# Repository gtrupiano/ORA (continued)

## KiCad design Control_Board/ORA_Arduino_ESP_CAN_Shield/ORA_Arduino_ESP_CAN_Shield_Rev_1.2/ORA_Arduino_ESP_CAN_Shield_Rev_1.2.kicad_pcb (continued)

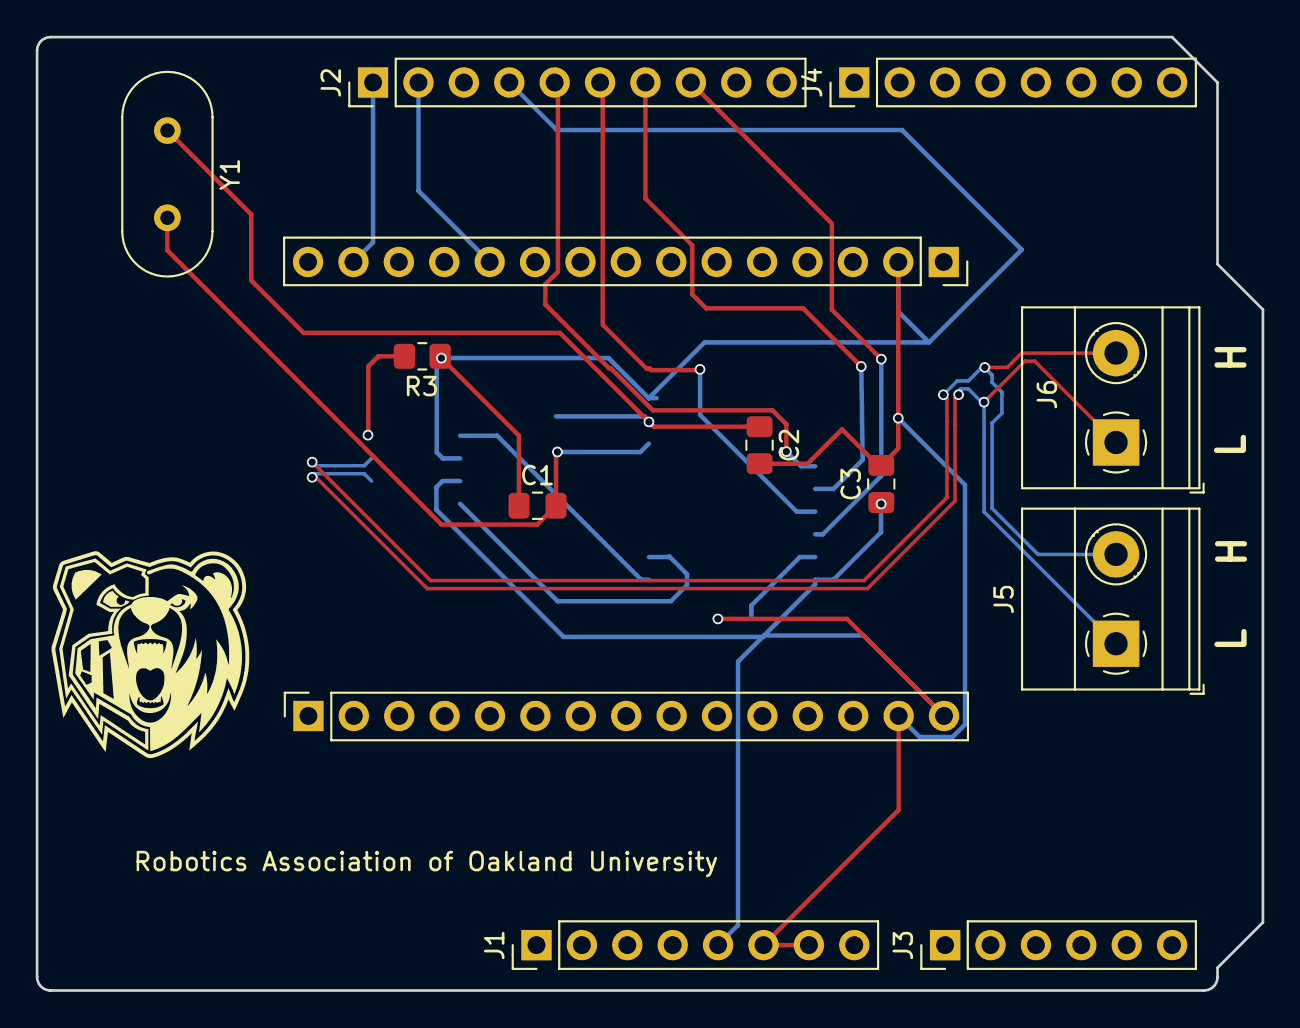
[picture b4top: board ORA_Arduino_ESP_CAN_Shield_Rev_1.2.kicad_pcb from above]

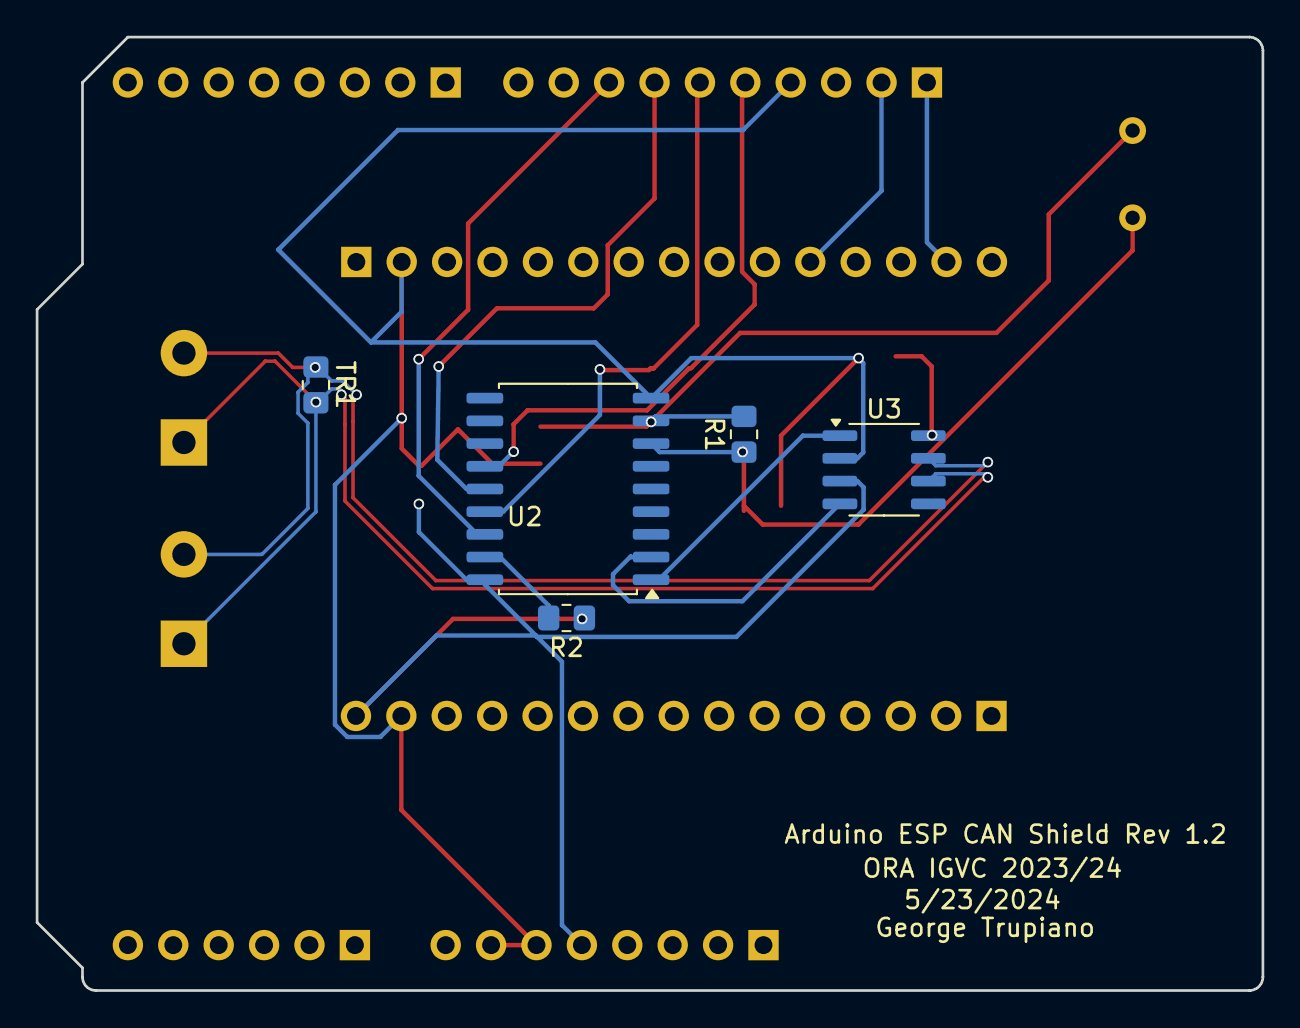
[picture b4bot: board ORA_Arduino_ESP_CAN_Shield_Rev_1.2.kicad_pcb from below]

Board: 2 copper layers, 68.6 x 53.3 mm, 17 parts (5 on the bottom side), 16 nets.

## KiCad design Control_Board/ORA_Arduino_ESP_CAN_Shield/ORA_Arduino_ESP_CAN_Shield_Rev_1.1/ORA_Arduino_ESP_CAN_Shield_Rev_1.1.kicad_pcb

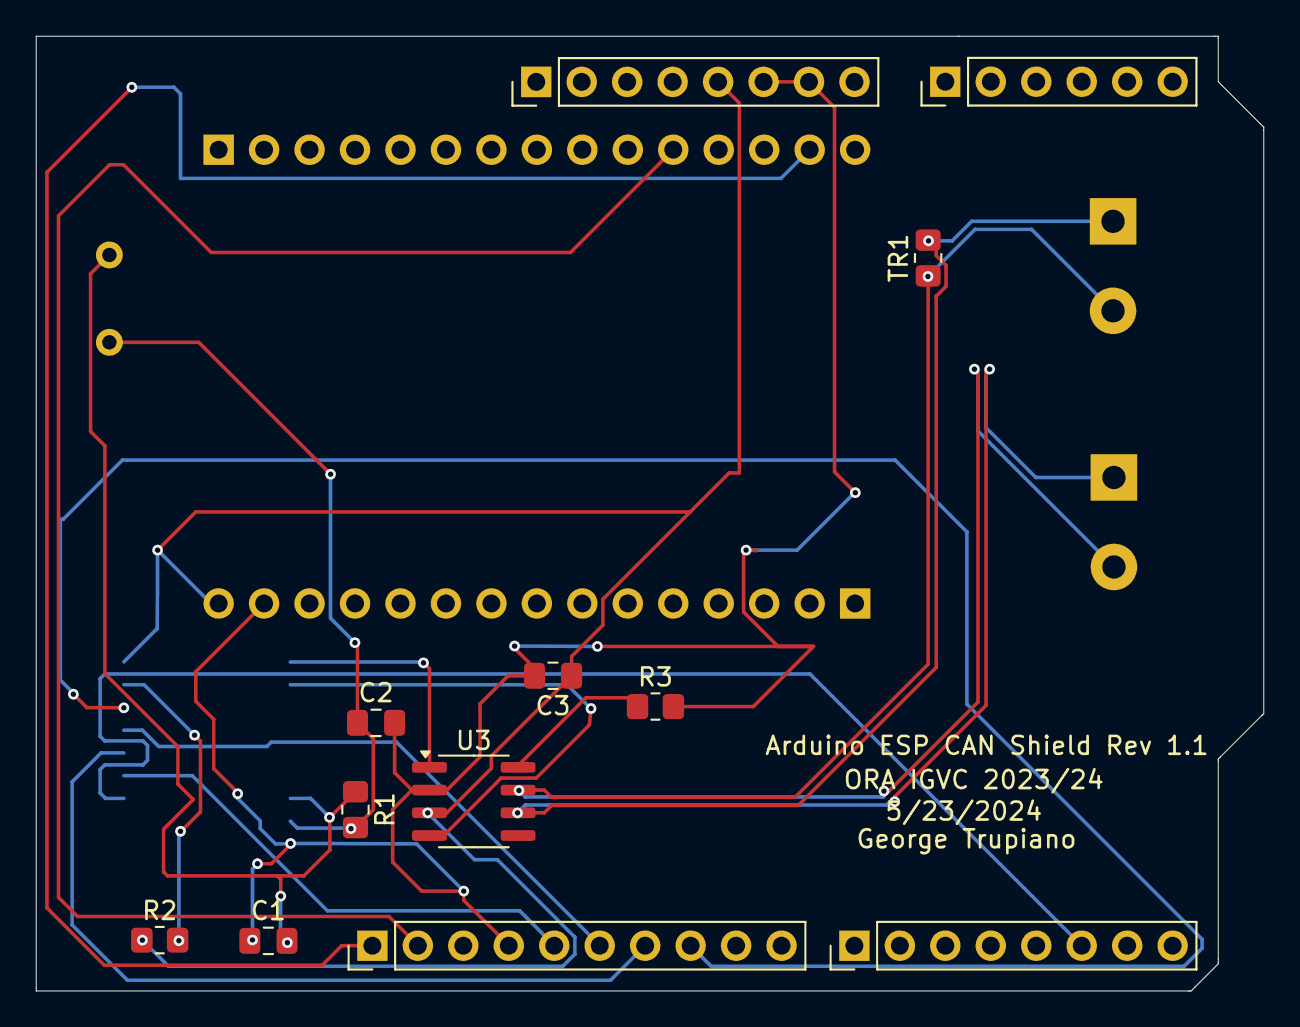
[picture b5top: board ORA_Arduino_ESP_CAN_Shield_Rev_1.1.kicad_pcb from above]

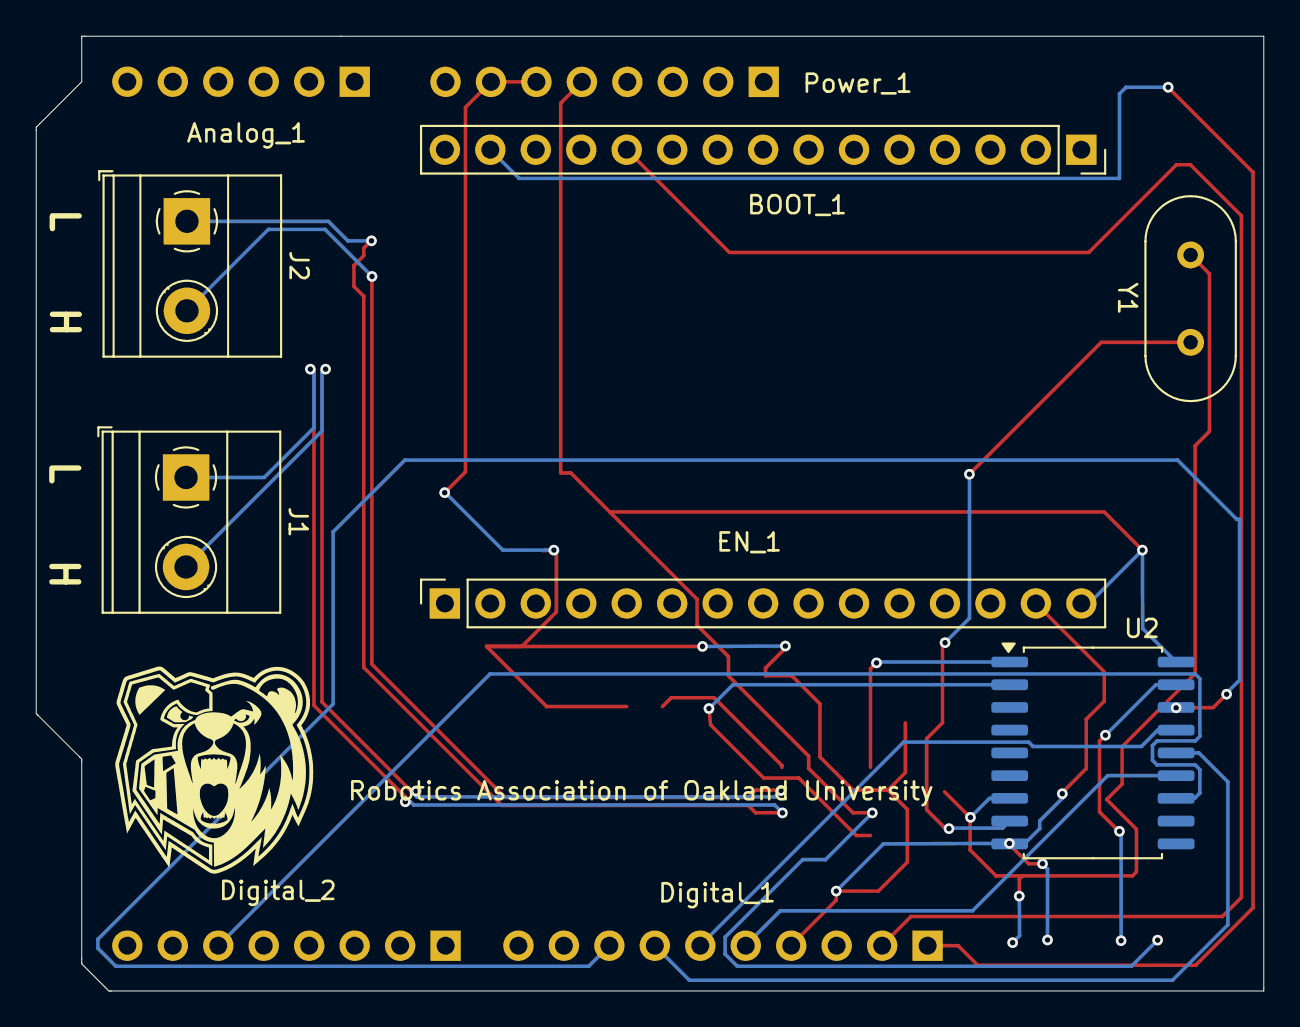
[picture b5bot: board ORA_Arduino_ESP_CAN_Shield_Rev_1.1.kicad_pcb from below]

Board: 2 copper layers, 68.6 x 53.3 mm, 18 parts (6 on the bottom side), 17 nets.

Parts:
Analog_1: Conn_01x06; PinHeader_1x06_P2.54mm_Vertical
BOOT_1: Conn_01x15; PinSocket_1x15_P2.54mm_Vertical
C1, C2: 22pF; C_0805_2012Metric_Pad1.18x1.45mm_HandSolder
C3: 100nF; C_0805_2012Metric_Pad1.18x1.45mm_HandSolder
Digital_1: Conn_01x10; PinHeader_1x10_P2.54mm_Vertical
Digital_2: Conn_01x08; PinHeader_1x08_P2.54mm_Vertical
EN_1: Conn_01x15; PinSocket_1x15_P2.54mm_Vertical
J1, J2: CAN; TerminalBlock_Phoenix_MKDS-1,5-2_1x02_P5.00mm_Horizontal
Power_1: Conn_01x08; PinHeader_1x08_P2.54mm_Vertical
R1: 1M; R_0805_2012Metric_Pad1.20x1.40mm_HandSolder
R2, R3: 10k; R_0805_2012Metric_Pad1.20x1.40mm_HandSolder
TR1: 120; R_0805_2012Metric_Pad1.20x1.40mm_HandSolder
U2: MCP2515-xSO; SOIC-18W_7.5x11.6mm_P1.27mm
U3: MCP2551-I-SN; SOIC-8_3.9x4.9mm_P1.27mm
Y1: 8Mhz; Crystal_HC49-4H_Vertical

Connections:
+5V: C3.1, EN_1.15, Power_1.5, R2.1, U2.18 (VDD), U3.3 (VDD)
CAN+: J1.2, J2.2, TR1.1, U3.7 (CANH)
CAN-: J1.1, J2.1, TR1.2, U3.6 (CANL)
CS: Digital_1.8, U2.16 (~CS)
GND: C1.1, C2.2, C3.2, Digital_1.4, EN_1.14, Power_1.6, Power_1.7, R3.2, U2.9 (VSS), U3.2 (VSS)
INT: Digital_2.6, U2.12 (~INT)
unnamed: C2.1, R1.2, U2.8 (OSC1), Y1.1
unnamed: C1.2, R1.1, U2.7 (OSC2), Y1.2
unnamed: U2.2 (RXCAN), U3.4 (RXD)
unnamed: U2.1 (TXCAN), U3.1 (TXD)
unnamed: R2.2, U2.17 (~RESET)
unnamed: R3.1, U3.8 (Rs)
SCK: Digital_1.5, U2.13 (SCK)
SCL: BOOT_1.14, Digital_1.1
SDA: BOOT_1.11, Digital_1.2
SI: Digital_1.7, U2.14 (SI)
SO: Digital_1.6, U2.15 (SO)

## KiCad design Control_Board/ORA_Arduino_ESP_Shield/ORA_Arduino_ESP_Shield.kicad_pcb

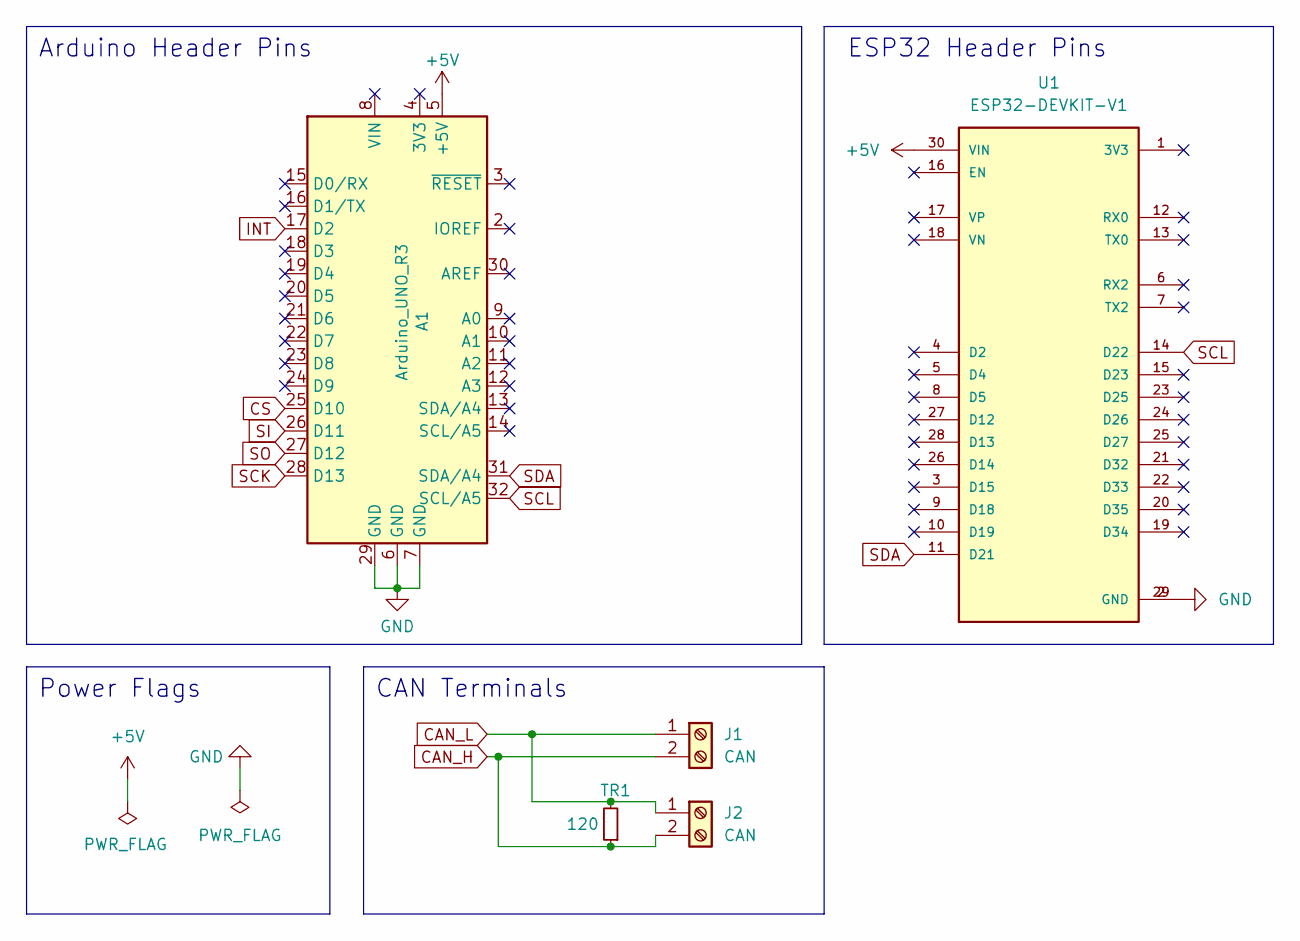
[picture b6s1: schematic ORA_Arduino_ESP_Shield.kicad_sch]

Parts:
A1: Arduino_UNO_R3
J1, J2: CAN; TerminalBlock_Phoenix_MKDS-1,5-2_1x02_P5.00mm_Horizontal
TR1: 120; R_0805_2012Metric_Pad1.20x1.40mm_HandSolder
U1: ESP32-DEVKIT-V1; ESP32_DEVKIT_V1_MODULE; PARTREV N/A

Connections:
+5V: A1.5 (+5V), U1.30 (VIN)
CAN_H: J1.2, J2.2, TR1.1
CAN_L: J1.1, J2.1, TR1.2
CS: A1.25 (D10)
GND: A1.6 (GND), A1.7 (GND), A1.29 (GND), U1.2 (GND), U1.29 (GND)
INT: A1.17 (D2)
SCK: A1.28 (D13)
SCL: A1.32 (SCL/A5), U1.14 (D22)
SDA: A1.31 (SDA/A4), U1.11 (D21)
SI: A1.26 (D11)
SO: A1.27 (D12)

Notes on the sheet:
Power Flags
Arduino Header Pins
CAN Terminals
ESP32 Header Pins

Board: 2 copper layers, 5 parts (1 on the bottom side), 6 nets, no tracks yet.

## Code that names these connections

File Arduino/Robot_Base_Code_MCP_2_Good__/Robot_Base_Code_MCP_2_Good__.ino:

#include <PS4Controller.h>
#include <mcp_can.h>
#include <SPI.h>

// digital pins available on control board: 0, 1, 10, 5, 13
// analog pins available on control board: 0, 1, 2, 3, 4

// CAN / ODrive Declarations
#define ODRV0_NODE_ID 0 // Left Motor
#define ODRV1_NODE_ID 1 // Right Motor
#define CAN0_INT 2    // Set INT to pin 2 (This is the Interrupt pin)
#define CAN_BAUDRATE 500000
MCP_CAN CAN0(17);   // Set CS to pin 17 (This is the Chip select)

#define EStop 0         // Hardware EStop

// IMU Declarations
#define IMU_SCL 3 // On AtMega32U4 Connected to Pin 18 (PD0)
#define IMU_SDA 2 // On AtMega32U4 Connected to Pin 19 (PD1)

// LED Declarations
#define LEDPWR_R 4 // On AtMega32U4 Connected to Pin 25 (PD4)
#define LEDPWR_G 12 // On AtMega32U4 Connected to Pin 26 (PD6)
#define LEDPWR_B 6 // On AtMega32U4 Connected to Pin 27 (PD7)

// Battery Voltage Detection Declaration
#define Battery_Voltage A0 // On AtMega32U4 Connected to Pin 27 (PF0)

double verticalMov = 0;
double horizontalMov = 0;
bool EStopButton = false;
bool EStopState = false;

void setup()
{
  pinMode(CAN0_INT, INPUT);

  pinMode(IMU_SCL, INPUT);
  pinMode(IMU_SDA, INPUT);

  pinMode(LEDPWR_R, INPUT);
  pinMode(LEDPWR_G, INPUT);
  pinMode(LEDPWR_B, INPUT);

  Serial.begin(115200);

  // MAC Address for my controller
  PS4.begin("bc:03:58:28:67:42");
  Serial.println("Ready");

  // Continuously tries to establish connection to MCP chip until it does
  while(1)
  {
    // Tries to initialize MCP CAN chip with clock of 8MHz and data transfer speed is 500KB/second
    if(CAN0.begin(MCP_ANY, CAN_500KBPS, MCP_8MHZ) == CAN_OK)
    {
      Serial.println("MCP2515 Initialized Successfully!");
      break;
    }
    else 
    {
      Serial.println("Error Initializing MCP2515...");
      delay(20);
    }
  }
}

void loop() 
{
  // For obtaining values, have arduino and esp work seperatly. Use I2C for communicating between the two
  if(PS4.isConnected()) // could combine with If statement below but this is easier to read for now
  {
    verticalMov = PS4.LStickY(); // Possibly add some error detection (debounce)?
    horizontalMov = PS4.LStickX();
    EStopButton = PS4.R1();

    Serial.print("X: ");
    Serial.print(verticalMov);
    Serial.print("  Y: ");
    Serial.println(horizontalMov);
  }
  else
  {
    verticalMov = 0;
    horizontalMov = 0;
  }

  // Allows EStop to be toggled
  if(EStopButton && !EStopState)
  {
    // Send EStop command to ODrive
    ODriveEStop();
    EStopState = true;
  }
  else if(EStopButton && EStopState)
  {
    ODriveControlState();
    ODriveMovement(verticalMov, horizontalMov);
    EStopState = false;
  }
}

// Converts Joystick values into Revolutions/Second and sends data to ODrive over CAN
void ODriveMovement(double verticalVelocity, double horizontalVelocity) // redo math for turns/second
{
  // Scales inputs
  verticalVelocity = constrain(verticalVelocity, -1.0, 1.0);
  horizontalVelocity = constrain(horizontalVelocity, -1.0, 1.0);

  // Standard for differential drive control
  double leftMotorVel = verticalVelocity - horizontalVelocity;
  double rightMotorVel = verticalVelocity + horizontalVelocity;

  // Converts the velocity requested into Revolutions / second
  const int maxVelocity = 5; // IGVC rules, should be meters/second units but not sure
  const double wheelCircumference = 2 * M_PI * 0.1524; // Circumference of the wheel in meters
  double leftMotorRPS= (leftMotorVel * maxVelocity) / wheelCircumference; // Turns/second
  double rightMotorRPS = (rightMotorVel * maxVelocity) / wheelCircumference; // Turns/second

  // Send velocity CAN commands to left and right motors
  CAN0.sendMsgBuf((ODRV0_NODE_ID << 5 | 0x0D), 0, 4, (byte*)&leftMotorRPS); // check 4
  CAN0.sendMsgBuf((ODRV1_NODE_ID << 5 | 0x0D), 0, 4, (byte*)&rightMotorRPS);
}

// Send CAN command to ODrive to initate EStop
void ODriveEStop()
{
  CAN0.sendMsgBuf((ODRV0_NODE_ID << 5 | 0x02), 0, 0, nullptr);
  CAN0.sendMsgBuf((ODRV1_NODE_ID << 5 | 0x02), 0, 0, nullptr);
  Serial.println("EStop Activated");
}

// Send CAN command to put axis into closed loop control state
void ODriveControlState() // Could combine with estop function but meh
{
  CAN0.sendMsgBuf((ODRV0_NODE_ID << 5 | 0x07), 0, 4, (byte*)"\x08");
  CAN0.sendMsgBuf((ODRV1_NODE_ID << 5 | 0x07), 0, 4, (byte*)"\x08");
  Serial.println("Put into closed loop control state");
}

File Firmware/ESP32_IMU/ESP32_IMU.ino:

/*
 **********************************************************************
 * INCLUDES
 **********************************************************************
*/

#include "ESP32_IMU.hpp"

/*
 **********************************************************************
 * DEFINES and CONSTANTS
 **********************************************************************
*/

/*
 **********************************************************************
 * GLOBAL VARIABLES
 **********************************************************************
*/

TaskTime_t tasks = 
{
    // {period, lastTime}
    .printImu = {60, 0},
    .led = {500, 0}
};

IMU_t imu = {};
BNO08x bno;

/*
 **********************************************************************
 * LOCAL TYPES
 **********************************************************************
*/

/*
 **********************************************************************
 * LOCAL VARIABLES (declare as static)
 **********************************************************************
*/

/*
 **********************************************************************
 * LOCAL FUNCTION PROTOTYPES (declare as static)
 **********************************************************************
*/
  
/*
 **********************************************************************
 * GLOBAL FUNCTIONS
 **********************************************************************
*/


void setup() 
{
    Serial.begin(115200);

    pinMode(LED_PIN, OUTPUT);

    // Setting up IMU
    bool imuConfigSuccessful = configureIMU();

    if(imuConfigSuccessful == false)
    {
        while(1)
        {
            Serial.println("An issue occured during configuration. Please look at serial logs to determine error and then try again.");
            delay(5000);
        }
    }
    else
    {
        Serial.println("IMU ready!");
    }
    
    delay(100);

    // Configuring all tasks last updated time
    unsigned long currTime = millis();
    tasks.printImu.lastTime = currTime;
    tasks.led.lastTime = currTime;

}


void loop() 
{
    /*
        Since IMU update needs to be called frequently so fusion filter 
        can be computed, other slower tasks need to be kept track of
        in terms of their timing. So checking the time of them is needed.
    */
    unsigned long currentTime = millis();

    if (bno.wasReset()) 
    {
        Serial.print("Sensor was reset ");
        imuOutputDataConfig();
    }

    // Fetching data from IMU and updating IMU struct
    updateImuObject();

    // Only print data when time proper amount of time has elapsed
    if((currentTime - tasks.printImu.lastTime) >= tasks.printImu.period)
    {
        bool printAccel = true; 
        bool printGyro = true;
        bool printQuat = true;

        printImuData(printAccel, printGyro, printQuat);
        
        // Updating time here since it is possible that when it's time to print data, that the IMU wasn't ready to update.
        tasks.printImu.lastTime = currentTime;
    }

    if((currentTime - tasks.led.lastTime) >= tasks.led.period)
    {
        digitalWrite(LED_PIN, !digitalRead(LED_PIN));
        tasks.led.lastTime = currentTime;
    }

    // Quaternions are computed by the fusion filter and only update when mpu.update() runs frequently. 
    // Keep loop fast; avoid long delays or quat may freeze at (1,0,0,0). 
    delay(1);
}


/*
 **********************************************************************
 * LOCAL FUNCTIONS
 **********************************************************************
*/

/**************************************************
 * Function Name: configureIMU
 * Description: 
**************************************************/

bool configureIMU()
{
    // Configuring communication over I2C
    Wire.begin(IMU_SDA_PIN, IMU_SCL_PIN);
    Wire.setClock(400000);   // 400 kHz I2C fast mode
    Wire.setTimeOut(50);     // prevent long I2C blocking/hanging
    
    delay(250);
    // TODO: Add in a multi attempt to connect to the bno
    
    uint8_t imuConnectAttempts = 0;
    bool imuConnected = false;

    while(imuConnectAttempts < IMU_CONNECT_RETRY_NUM)
    {
        // Setting up IMU with proper interrupt and reset pins
        if(bno.begin(IMU_I2C_ADDRESS, Wire, IMU_INT_PIN, IMU_RST_PIN) == false) 
        {
            Serial.println("IMU connection failed. Please check connection with examples.");
        }
        else
        {
            Serial.println("IMU connection successful");
            imuConnected = true;
            break;
        }

        imuConnectAttempts++;
    }

    // Configuring what data to report
    imuOutputDataConfig();

    return imuConnected;
}


/**************************************************
 * Function Name: imuOutputDataConfig
 * Description: 
**************************************************/

void imuOutputDataConfig()
{
    // Accelerometer data
    if(bno.enableAccelerometer() == true)
    {
        Serial.println("Accelerometer enabled");
    }
    else
    {
        Serial.println("Can't enable  accelerometer");
    }

    // Gyroscopic data
    if(bno.enableGyro() == true)
    {
        Serial.println("Gyro enabled");
    }
    else
    {
        Serial.println("Can't enable  gyro");
    }

    // Rotational vector data (used for quaternions)
    if(bno.enableRotationVector() == true)
    {
        Serial.println(("Rotation vector enabled"));
    }
    else
    {
        Serial.println("Can't enable  rotation vector");
    }
}

/**************************************************
 * Function Name: updateImuObject
 * Description: 
**************************************************/

void updateImuObject()
{
    // Checking whether an event occured
    if(bno.getSensorEvent() == true)
    {
        uint8_t sensorEvent = bno.getSensorEventID();

        switch(sensorEvent)
        {
            case SENSOR_REPORTID_ACCELEROMETER:
                imu.accel.x = bno.getAccelX();
                imu.accel.y = bno.getAccelY();
                imu.accel.z = bno.getAccelZ();
            break;

            case SENSOR_REPORTID_GYROSCOPE_CALIBRATED:
                imu.gyro.x = bno.getGyroX();
                imu.gyro.y = bno.getGyroY();
                imu.gyro.z = bno.getGyroZ();
            break;

            case SENSOR_REPORTID_ROTATION_VECTOR:
                imu.quat.w = bno.getQuatReal();
                imu.quat.x = bno.getQuatI();
                imu.quat.y = bno.getQuatJ();
                imu.quat.z = bno.getQuatK();
                // there is a getQuatRadianAccuracy() but not sure if needed?
            break;

            default:
            break;
        }

        imu.sampleTimeMS = millis();
    }
}


/**************************************************
 * Function Name: printImuData
 * Description: 
**************************************************/

void printImuData(bool accel, bool gyro, bool quat)
    {
    // Printing acceleration data
    if(accel)
    {
        Serial.print("[");
        Serial.print(imu.sampleTimeMS);
        Serial.print("] Acceleration (x,y,z): ");
        Serial.print("X: ");
        Serial.print(imu.accel.x);
        Serial.print(", Y: ");
        Serial.print(imu.accel.y);
        Serial.print(", Z: ");
        Serial.print(imu.accel.z);
        Serial.println(" m/s^2");
        Serial.println();
    }

    // Printing gyroscopic data
    if(gyro)
    {
        Serial.print("[");
        Serial.print(imu.sampleTimeMS);
        Serial.print("] Gyroscope (x,y,z): ");
        Serial.print("X: ");
        Serial.print(imu.gyro.x);
        Serial.print(", Y: ");
        Serial.print(imu.gyro.y);
        Serial.print(", Z: ");
        Serial.print(imu.gyro.z);
        Serial.println(" rad/s");
        Serial.println();
    }

    // Printing quaternion data
    if(quat)
    {
        Serial.print("[");
        Serial.print(imu.sampleTimeMS);
        Serial.print("] Quaternion (w,x,y,z): ");
        Serial.print(imu.quat.w, 6); Serial.print(", ");
        Serial.print(imu.quat.x, 6); Serial.print(", ");
        Serial.print(imu.quat.y, 6); Serial.print(", ");
        Serial.println(imu.quat.z, 6);
        Serial.println();
    }
    
    // Ending line if any value are requested
    if(accel || gyro || quat)
    {
        Serial.println("--------------------------");
        Serial.println();
    }
}

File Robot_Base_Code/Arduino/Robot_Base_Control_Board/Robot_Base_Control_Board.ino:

// States
bool EStopped = false;
bool AutonMode = false;

// Inputs
const int EStopPin = 0;
const int AutonPin = 1;

// Outputs
const int LED_R = 4;
const int LED_G = 12;
const int LED_B = 6;

// Blinking Declarations
unsigned long prevRunTime = 0;
const int blinkInterval = 200;
bool autonLEDState = false;
void AutonRedBlink();
void setup() 
{
  pinMode(EStopPin, INPUT);  // Configure EStop as input signal
  pinMode(AutonPin, INPUT);  // Configure Auton as input signal

  pinMode(LED_R, OUTPUT);
  pinMode(LED_G, OUTPUT);
  pinMode(LED_B, OUTPUT);

  // Initialize LED states
  digitalWrite(LED_R, LOW);
  digitalWrite(LED_G, LOW);
  digitalWrite(LED_B, LOW);
}

void loop() 
{
  EStopped = digitalRead(EStopPin);  // Read the EStop signal
  AutonMode = digitalRead(AutonPin);  // Read the Auton signal

  if (EStopped) 
  { 
    digitalWrite(LED_R, HIGH);
    digitalWrite(LED_G, LOW);
    digitalWrite(LED_B, LOW);
  }
  else 
  { 
    if (AutonMode) 
    {
      AutonRedBlink();
    }
    else 
    {
      digitalWrite(LED_R, LOW);
      digitalWrite(LED_G, HIGH);
      digitalWrite(LED_B, LOW);
    }
  }
  delay(10);
}

void AutonRedBlink()
{
  digitalWrite(LED_B, LOW);
  digitalWrite(LED_G, LOW);

  unsigned long currRunTime = millis();

  if(currRunTime - prevRunTime >= blinkInterval)
  {
    autonLEDState = !autonLEDState;

    digitalWrite(LED_R, autonLEDState ? HIGH : LOW);

    prevRunTime = currRunTime;  // Update the previous run time after toggling
  }
}

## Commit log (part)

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2024-03-12 Base Code updates
2024-03-13 Second Revision
2024-03-13 Getting there?
2024-03-14 Notes
2024-03-18 test
2024-03-19 Update Robot_Base_Code_MCP_2_Good__.ino
    Toggle function for E-Stop implemented
    Movement function adjusted for revolutions per second calculations.
    Declarations done for IMU, LED, etc.
2024-03-21 Library Update
2024-03-21 Made separate program for Control board and ESP32
2024-03-22 Continued
2024-03-23 Basic I2C programs created
    This was just to test whether inputs from controller could be received from ESP and transmitted through I2C to a separate Arduino.
2024-03-24 Deleted Library folder
    Not needed
2024-03-28 Working I2C program
    Controller values are able to be received from ESP and sent to arduino uno.
2024-03-29 Finished testing I2C programs
2024-03-29 Added proper I2C communication
2024-03-29 Comments
2024-04-03 Added control board and reformatting
2024-04-06 Created Robot Base Code using ODriveArduino Library
    Original MCP program was modified to incorperate ODriveArduino Library
2024-04-07 User input made and lib example updated
2024-04-07 Modified receive program
    ESP is being weird but arduino 2 arduino works for I2C
2024-04-08 Fixed data conversion issues
2024-04-08 fixed
2024-04-19 Commented program
2024-04-21 Made rev 2.1
    Still need rev 2
2024-04-21 Rev 2
2024-04-30 Renaming and reorganizing files
2024-04-30 Reorganize
2024-04-30 Renamed
2024-04-30 Renaming
2024-05-03 Added picture
2024-05-03 Pictures Added
2024-05-03 ZED Testing
2024-05-03 ZED Stuff
2024-05-06 Added File
2024-05-06 Rename test.md to Reformatted_README.md
2024-05-06 README Rework
2024-05-06 Added Positional Tracking Program
2024-05-06 Reformat
2024-05-07 Created new program that incorperates both motors
    Need to fix math for differential drive and variable names.
    Also test if both motors can be controlled using the logic that is set up.
    (setup function)
2024-05-07 Created new programs for testing dual motor control
2024-05-08 Added modified mini bot program
2024-05-10 Create Robot_Base_Arduino_Function_Cleanup.ino
    This is just a reformatted version of original program. Just tried to simplify program with additional functions.
2024-05-11 Added communication states for software
2024-05-12 Created Arduino ESP Shield
2024-05-13 Created ESP_CAN Shield and "Finished" ESP Shield
2024-05-13 Modified
2024-05-13 CAN Shield finished
2024-05-14 Modifications
2024-05-15 Finalizing board for ordering
2024-05-16 Final Revision of ESP and CAN shield
2024-05-17 Fixed issue with pin spacing and added revision that was ordered
2024-05-17 Finalized
2024-05-19 Edits
2024-05-22 Created Rev 2 with Stack light terminals
2024-05-23 Fixed errors in rev 1
    Issues include:
    misplaced esp pins, moved capacitor
    Improvements:
    Used proper footprints for ESP as well as arduino
2024-05-23 Fixed footprint issues for ESP
    Things to fix:
    Route CAN as differential pairs (How to split the pair)
2024-05-23 Fixed and ordered rev 1.1
2024-05-24 Rename README_ESP_CAN_Shield.md to README.md
2024-05-27 Gerber Files
2024-05-27 Fixed CAN IC Issues
    Changed oscillator capacitor values to 22pF, corrected reset for 2515 as active low (connected to 5V)
2024-05-27 Applied all legacy updates with CAN ICs from rev 1 to 1.2 and 2
2024-05-27 Made separate files for Rev 1.1 and Rev 1.15
    Rev 1.1 (which was ordered) had an error with the reset pin on the mcp 2515 chip. It should have been active low and not active high.
    Rev 1.15 has this issue fixed but isn't ordered
2024-05-27 Update Robot_Base_Arduino.ino
    Add the sending of autonomous state and add physical estop button logic (it should override the software estop aka, it should be the first and main determiner for whether the robot is in an estop sta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
2024-05-29 Added Rev 1.1 for control board
2024-05-29 Updated Rev 1.1 for control board
2024-05-31 Code Updates
2024-06-01 IGVS Changes
2024-06-02 IGVC Updates
2024-06-02 Updated programs
2024-06-04 Fixed Auton Issues and Debugging CAN Communication
    MCP Chip only allows 2 messages to be received at one time. Might try to do fifo or send the CAN messages directly from the ODrives
2025-01-21 New unified program
    Making unified program that only uses ESP32
2025-04-30 Made changes to data types for speeds and encoder data in order to match the library. Also, made changes to autonomous mode function to check all messages in the RX buffer and not just one message.
2025-05-31 Added local code from laptop
2026-02-22 Added Micro ROS program for publishing IMU data to topic
2026-02-23 Added micro ROS setup and run script to make using it easier. Modified gitignore for built items. Modified ESP32 program to have a retry functionality. Included the original ESP32 program for just th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
2026-02-25 Added calibration sequence for IMU. Fixed quaternion issue by increasing loop speed. This makes it harder for other tasks to be executed. May try to find other IMU.
2026-03-01 Refactored code to have task based execution. Also, set defined calibration values instead of recalibrating each time
2026-03-09 Updated MicroROS program to properly use IMU data.
2026-03-10 Updated Micro ROS program to include covariances. Fixed scripts to make them more generic to allow others to use them. Downgraded esp32 board library which fixed the topic update rate.
2026-03-10 Created README for the ESP32 IMU Micro ROS program.
2026-03-10 Fixed formatting in new README file.
    Added additional instructions for IMU data publishing and clarified software setup steps.
2026-03-14 Updated code to fix the skipping issue. This was a result of the feature that I implemented to stop stale data from being published to the message. As a result, the frequency of the messages was inco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
2026-03-14 Meant to fix last commit message. Removed feature that would only update ROS message if data was ready. This was to elimintate the potential for stale data. The issue with this was the timing for the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
2026-04-04 Restructured repo and added project for ESP board
2026-04-04 Added read me for ESP IMU PCB
2026-04-06 Finished schematic and started working on layout
2026-04-16 Added all datasheets for schematic. Created .md that describes where I looked in each datasheet for what piece of information. Finalized the schematic and got a good starting point for the layout.
2026-04-16 Fixed MD file image links.
2026-04-16 Fix image path in PCB Design Notes
    Updated image path for Boot Pins To Avoid in PCB design notes.
2026-04-23 Modified IMU MicroROS code to incorporate autonomous LED state service.
2026-04-25 Made changes to get autonomous LED service to fully work. This should be fully working code.
2026-04-25 Changed name of pins
2026-04-26 Eliminated tracking of .history file.
2026-04-26 Updated README for ESP32_MicroROS Program execution.
2026-04-26 Finished PCB layout. Added more detail to PCB design notes MD file.
2026-04-26 Started writing main README for repo.
2026-04-26 Modified README for software
2026-04-26 Generated fabrication files
2026-04-27 Updated PCB_Design_Notes.md file.
2026-04-27 Updated main README and Hardware README.
2026-04-29 Added boot button
2026-04-29 Updated gitignore for fabrication files.
2026-04-29 Cleaned up boot button implementation. Updated all images for README of schematic, layout, and model.
2026-04-29 Generation of PCB fabrication files.
2026-04-30 Canceled board because of mistakes. This is going to stink :)
2026-05-01 Reworked ESP_IMU_Board to fix the regulator issue, some layout inconsistancies, and footprint mismatches.
2026-05-02 Brief update to hardware README.
2026-05-09 Updated files to be all C++
2026-05-14 Updated ESP IMU code to work with the BNO086 chip. It currently is failing at the enabling of data outputs but I'm looking into that.
2026-05-14 There was an issue with the library where even if the data outputs were configured it would output that it failed. So I bypassed the error checking and it works.
2026-05-15 Added retry for IMU connection due to instability of the chip. Should be ready to port for micro-ROS
2026-05-15 Updated project README.
2026-05-15 Updated Firmware README
2026-05-15 Ported over new BNO086 code to the Micro_ROS code.
2026-05-17 Made modification for IMU MicroROS code:
    - Fixed issues with new BNO code.
    - Timing for reports are improved.
    - Made the reconnect more robust.
2026-05-27 Modified publisher and services to include name spaces.
2026-05-27 Changed name of LED timer before adding new timer for auton service.
2026-05-27 Made autonomous LED service blink LED.
2026-05-28 Fixed README for Firmware
2026-05-30 Fixed microROS code timing.
2026-05-30 Updated names
2026-05-30 Made auton timer basic and not microROS based. Fixed issues.
2026-06-03 Added audit files for issues in Rev A design.
2026-06-11 Modified system to operate under a higher baud rate which allows for IMU data to be published at 100Hz.
